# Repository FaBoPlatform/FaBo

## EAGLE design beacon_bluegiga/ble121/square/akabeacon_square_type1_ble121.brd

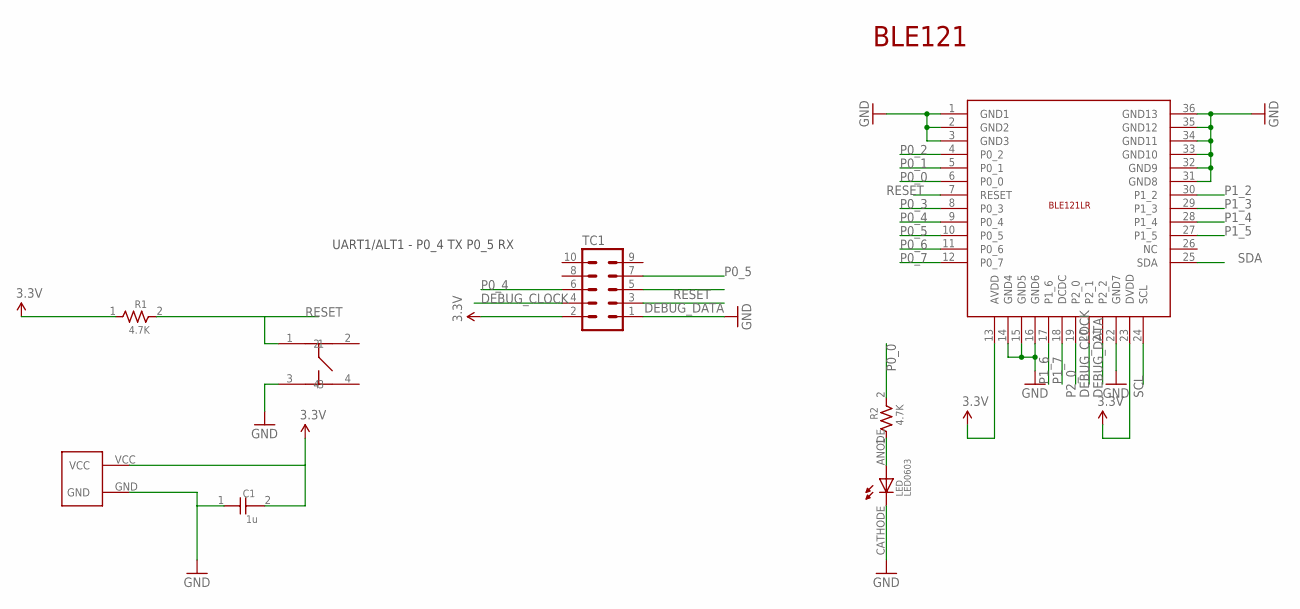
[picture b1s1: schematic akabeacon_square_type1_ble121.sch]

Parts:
BLE1: BLUEGIGA-BLE121LR
C1: 1u; 0603
LED: LED0603; 0603
R1, R2: 4.7K; 0603
TC1: TC2050-IDC-NL
U$2: SQUARE-TYPE1; SQUARE-TYPE1-TC2030
U$6: SWICTH-4P(KMR2); SWITCH-4P(KMR2)

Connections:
3.3V: BLE1.13 (AVDD), BLE1.23 (DVDD), C1.2, R1.1, TC1.2, U$2.VCC
DEBUG_CLOCK: BLE1.20 (P2_1), TC1.4
DEBUG_DATA: BLE1.21 (P2_2), TC1.3
GND: BLE1.1 (GND1), BLE1.2 (GND2), BLE1.3 (GND3), BLE1.22 (GND7), BLE1.31 (GND8), BLE1.32 (GND9), BLE1.33 (GND10), BLE1.34 (GND11), BLE1.35 (GND12), BLE1.36 (GND13), C1.1, LED.CATHODE, TC1.1, U$2.GND, U$6.3
unnamed: LED.ANODE, R2.1
unnamed: BLE1.14 (GND4), BLE1.15 (GND5), BLE1.16 (GND6)
P0_0: BLE1.6 (P0_0), R2.2
P0_1: BLE1.5 (P0_1)
P0_2: BLE1.4 (P0_2)
P0_3: BLE1.8 (P0_3)
P0_4: BLE1.9 (P0_4), TC1.6
P0_5: BLE1.10 (P0_5), TC1.7
P0_6: BLE1.11 (P0_6)
P0_7: BLE1.12 (P0_7)
P1_2: BLE1.30 (P1_2)
P1_3: BLE1.29 (P1_3)
P1_4: BLE1.28 (P1_4)
P1_5: BLE1.27 (P1_5)
P1_6: BLE1.17 (P1_6)
P1_7: BLE1.18 (DCDC)
P2_0: BLE1.19 (P2_0)
RESET: BLE1.7 (RESET), R1.2, TC1.5, U$6.1
SCL: BLE1.24 (SCL)
SDA: BLE1.25 (SDA)

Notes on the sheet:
BLE121
UART1/ALT1 - P0_4 TX P0_5 RX

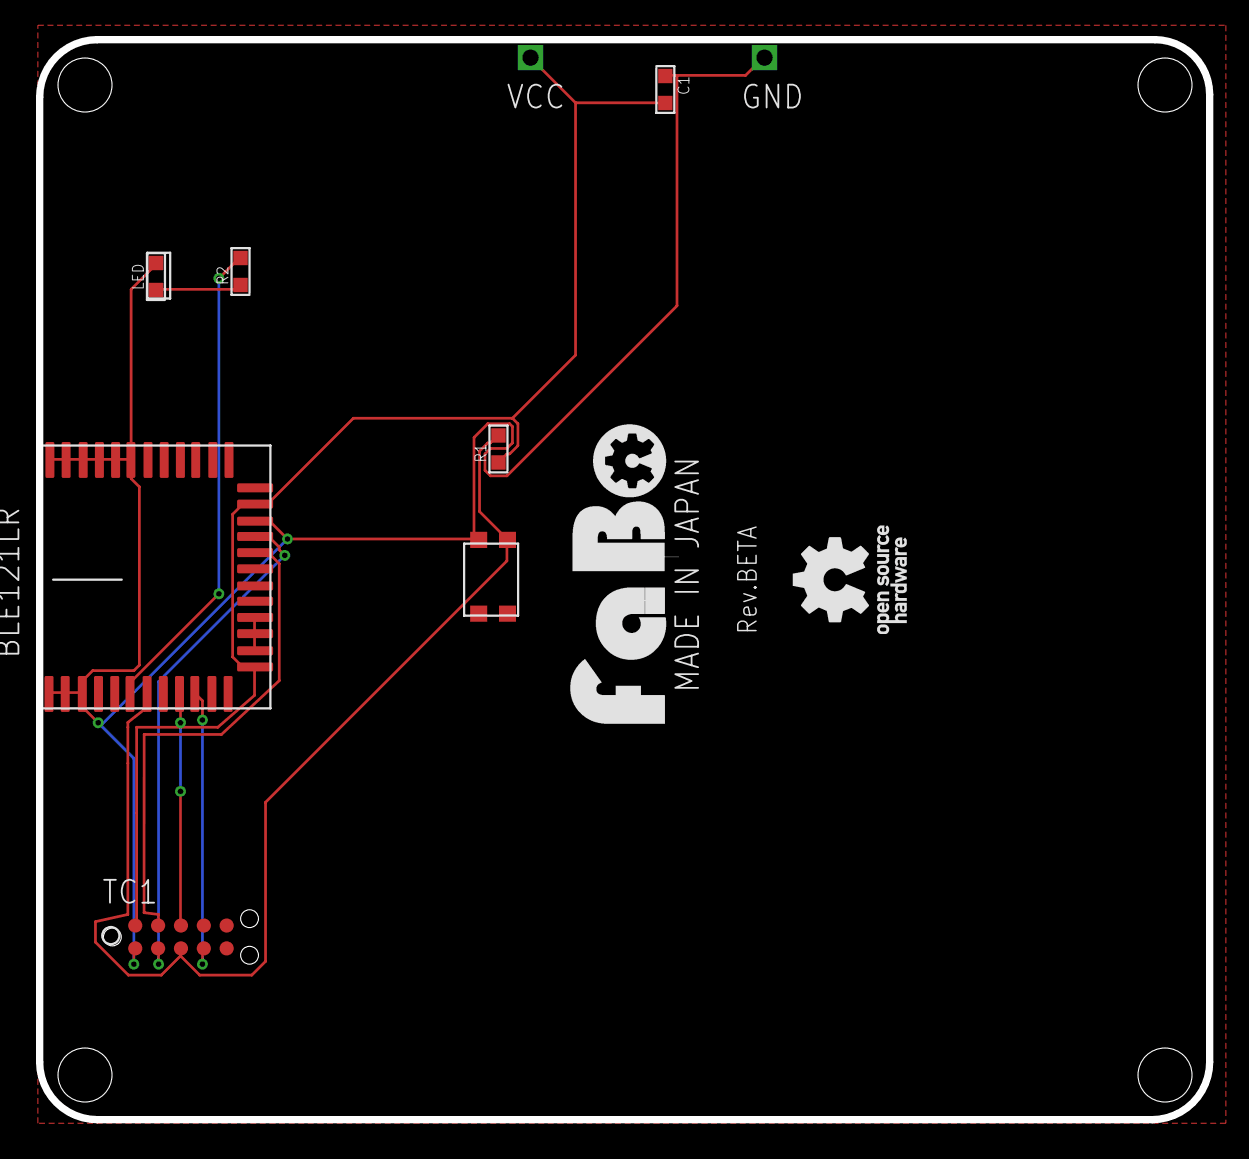
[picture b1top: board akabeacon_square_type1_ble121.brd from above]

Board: 2 copper layers, 65.0 x 60.0 mm, 8 parts (0 on the bottom side), 10 nets.

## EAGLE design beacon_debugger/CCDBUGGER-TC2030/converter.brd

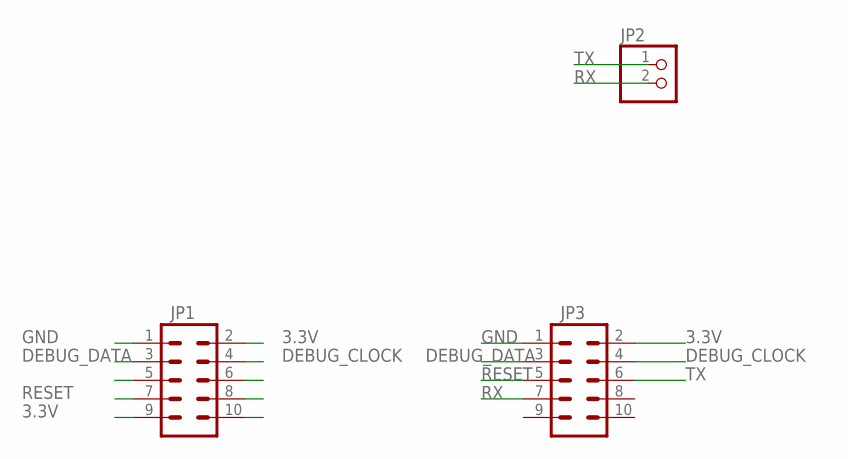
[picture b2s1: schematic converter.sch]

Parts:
JP1, JP3: M05X2SHD; 2X5-SHROUDED
JP2: PINHD-1X2; 1X02

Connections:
3.3V: JP1.2, JP1.9, JP3.2
CSN: JP1.5
DEBUG_CLOCK: JP1.4, JP3.4
DEBUG_DATA: JP1.3, JP3.3
GND: JP1.1, JP3.1
MISO: JP1.10
MOSI: JP1.8
RESET: JP1.7, JP3.5
RX: JP2.2, JP3.7
SCLK: JP1.6
TX: JP2.1, JP3.6

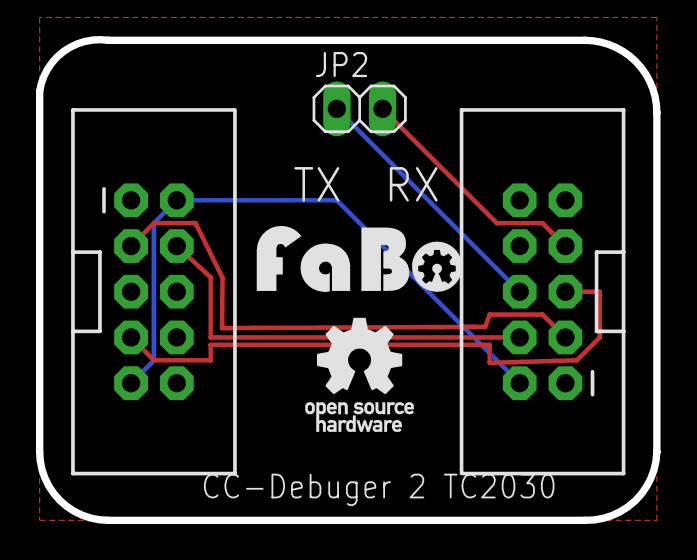
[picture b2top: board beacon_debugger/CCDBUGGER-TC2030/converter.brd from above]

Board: 2 copper layers, 34.3 x 26.7 mm, 5 parts (0 on the bottom side), 7 nets.

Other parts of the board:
U$1: LOGO_FABO_M
U$2: LOGO_OSHW_T_M

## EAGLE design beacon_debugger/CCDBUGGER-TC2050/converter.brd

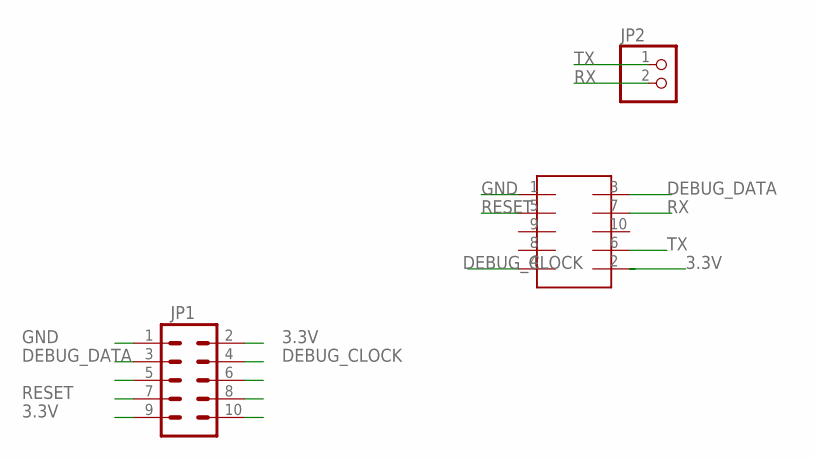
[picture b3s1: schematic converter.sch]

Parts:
JP1: M05X2SHD; 2X5-SHROUDED
JP2: PINHD-1X2; 1X02
U$4: TC-2050-SOCKET

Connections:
3.3V: JP1.2, JP1.9, U$4.2
CSN: JP1.5
DEBUG_CLOCK: JP1.4, U$4.4
DEBUG_DATA: JP1.3, U$4.3
GND: JP1.1, U$4.1
MISO: JP1.10
MOSI: JP1.8
RESET: JP1.7, U$4.5
RX: JP2.2, U$4.7
SCLK: JP1.6
TX: JP2.1, U$4.6

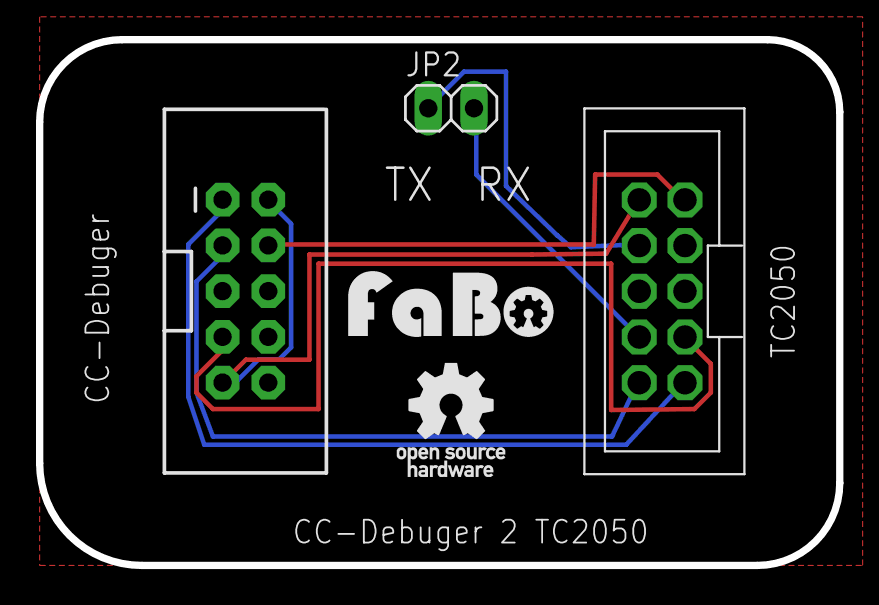
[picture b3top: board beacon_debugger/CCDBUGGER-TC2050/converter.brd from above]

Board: 2 copper layers, 44.4 x 29.2 mm, 5 parts (0 on the bottom side), 7 nets.

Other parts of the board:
U$1: LOGO_FABO_M
U$2: LOGO_OSHW_T_M

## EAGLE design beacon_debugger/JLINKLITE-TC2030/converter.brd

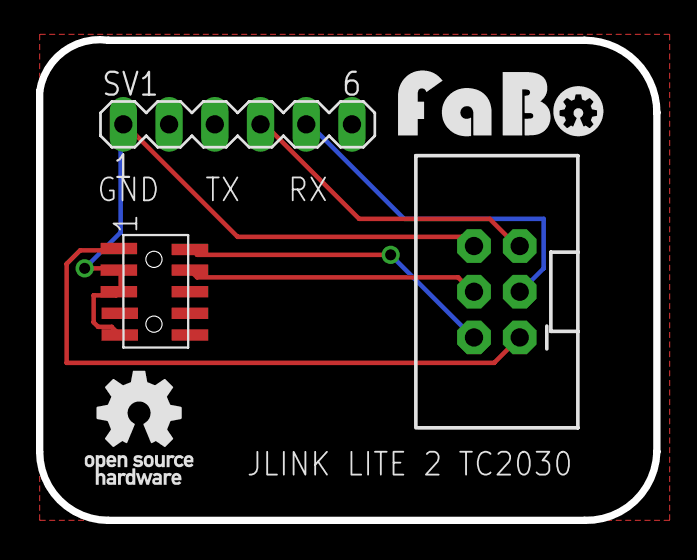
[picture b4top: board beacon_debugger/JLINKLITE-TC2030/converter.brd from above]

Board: 2 copper layers, 34.3 x 26.7 mm, 5 parts (0 on the bottom side), 6 nets.

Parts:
JP2: 2X3-SHROUDED
SV1: MA06-1
U$1: LOGO_FABO_M
U$2: LOGO_OSHW_T_M
U$5: PIN-HEADER-SMT(1.27MM)2X5

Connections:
3.3V: JP2.1, U$5.1
GND: JP2.6, SV1.1, U$5.3, U$5.5, U$5.9
P0_4: JP2.5, SV1.4
P0_5: JP2.3, SV1.5
SWCLK: JP2.4, U$5.4
SWDIO: JP2.2, U$5.2

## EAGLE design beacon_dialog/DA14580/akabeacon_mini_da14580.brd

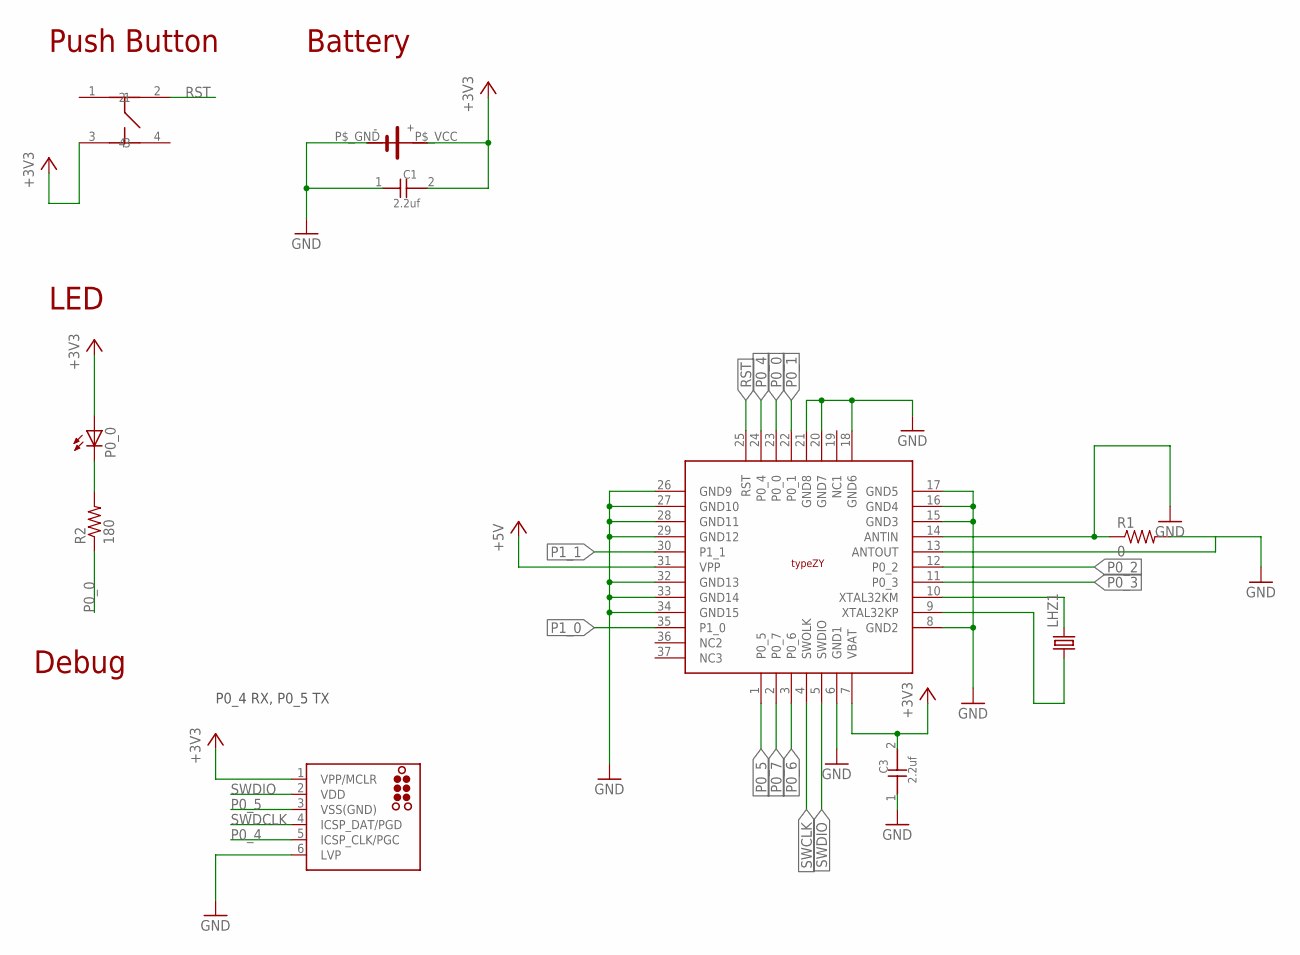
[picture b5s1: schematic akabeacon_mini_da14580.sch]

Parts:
C1, C3: 2.2uf; 0603
J2: TC2030-MCP
LHZ1: FC-12M
P0_0: LEDCHIP-LED0603; CHIP-LED0603
R1: 0; 0603-RES
R2: 180; 0603-RES
U$1: MURATA-TYPEZY; MURATA_TYPEZY
U$6: SMTU2450-BOTTOM-MINI
U$7: SWICTH-4P(KMR2); SWITCH-4P(KMR2)

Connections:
+3V3: C1.2, C3.2, J2.1 (VPP/MCLR), P0_0.A, U$1.7 (VBAT), U$6.P$_VCC, U$7.3
+5V: U$1.31 (VPP)
GND: C1.1, C3.1, J2.6 (LVP), R1.1, R1.2, U$1.6 (GND1), U$1.8 (GND2), U$1.14 (ANTIN), U$1.15 (GND3), U$1.16 (GND4), U$1.17 (GND5), U$1.18 (GND6), U$1.20 (GND7), U$1.21 (GND8), U$1.26 (GND9), U$1.27 (GND10), U$1.28 (GND11), U$1.29 (GND12), U$1.32 (GND13), U$1.33 (GND14), U$1.34 (GND15), U$6.P$_GND
LED1: P0_0.C, R2.2
P0_0: R2.1, U$1.23 (P0_0)
P0_1: U$1.22 (P0_1)
P0_2: U$1.12 (P0_2)
P0_3: U$1.11 (P0_3)
P0_4: J2.5 (ICSP_CLK/PGC), U$1.24 (P0_4)
P0_5: J2.3 (VSS(GND)), U$1.1 (P0_5)
P0_6: U$1.3 (P0_6)
P0_7: U$1.2 (P0_7)
P1_0: U$1.35 (P1_0)
P1_1: U$1.30 (P1_1)
RST: U$1.25 (RST), U$7.2
SWCLK: U$1.4 (SWOLK)
SWDCLK: J2.4 (ICSP_DAT/PGD)
SWDIO: J2.2 (VDD), U$1.5 (SWDIO)
XTAL32KM: LHZ1.2, U$1.10 (XTAL32KM)
XTAL32KP: LHZ1.1, U$1.9 (XTAL32KP)

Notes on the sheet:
Battery
Push Button
Debug
LED
P0_4 RX, P0_5 TX

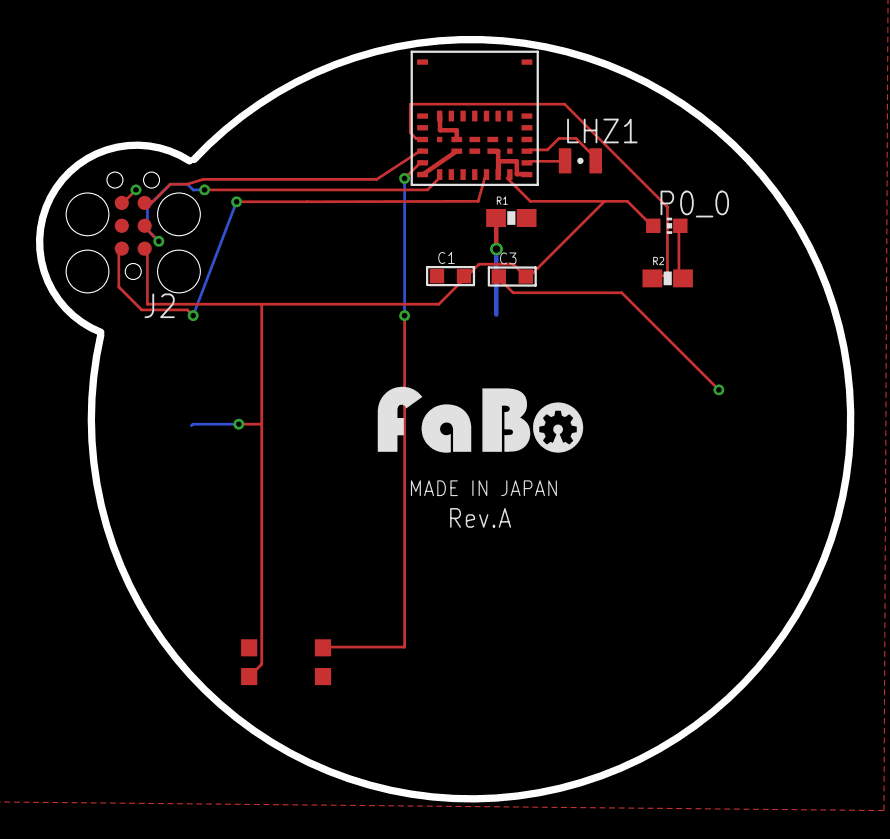
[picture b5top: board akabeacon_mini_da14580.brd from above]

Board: 2 copper layers, 45.1 x 42.2 mm, 11 parts (0 on the bottom side), 10 nets.

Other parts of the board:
U$2: LOGO_FABO_M

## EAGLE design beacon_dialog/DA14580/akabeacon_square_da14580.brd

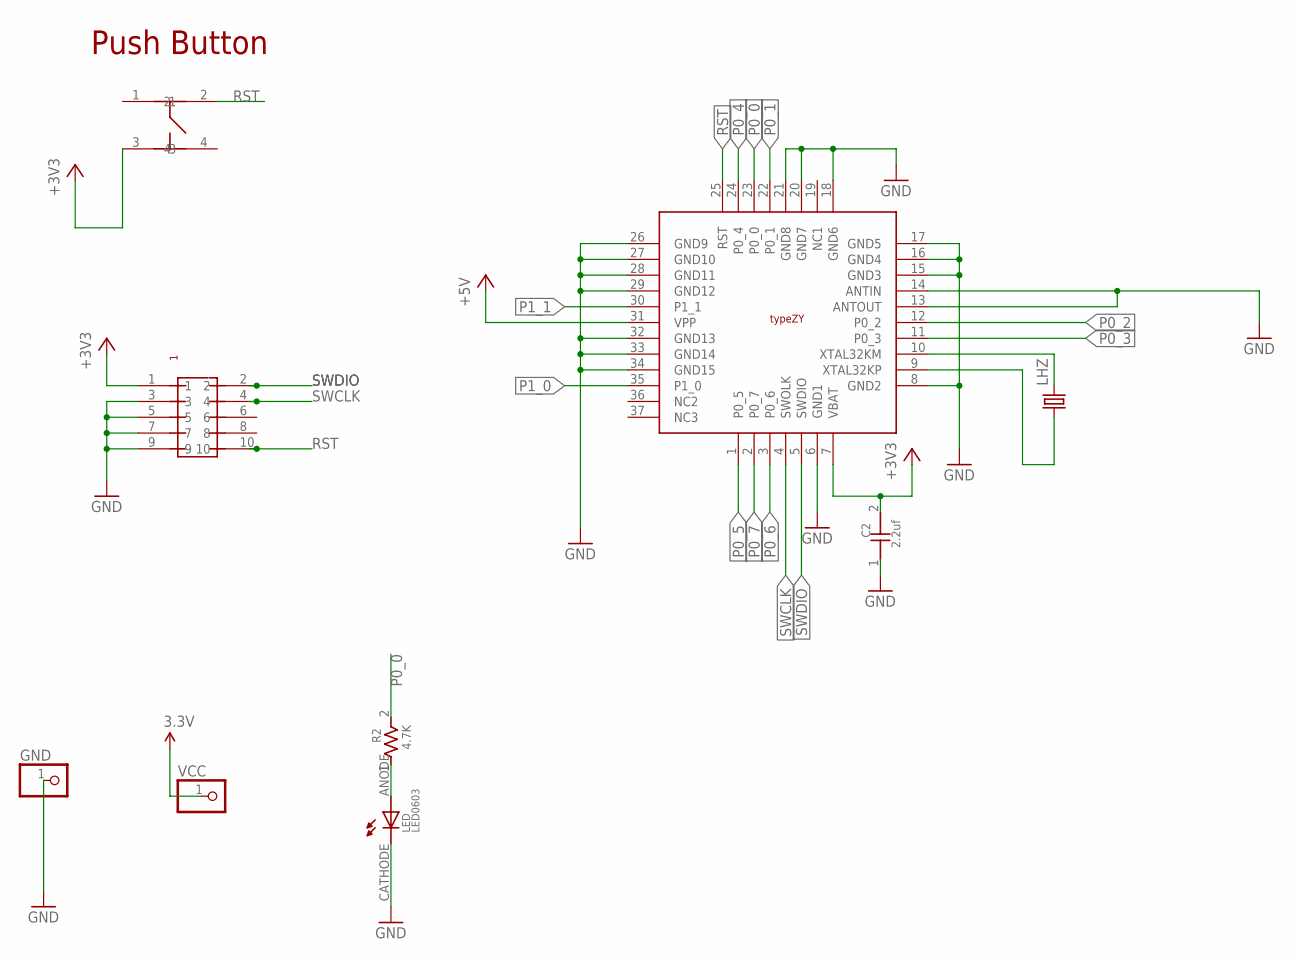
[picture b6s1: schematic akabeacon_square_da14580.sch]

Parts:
C2: 2.2uf; 0603
GND: PINHD-1X1CB; 1X01-CLEANBIG
LED: LED0603; 0603
LHZ: FC-12M
R2: 4.7K; 0603
U$6: PIN-HEADER-SMT(1.27MM)2X5
U$7: SWICTH-4P(KMR2); SWITCH-4P(KMR2)
U$9: MURATA-TYPEZY; MURATA_TYPEZY
VCC: PINHD-1X1CB; 1X01-CLEANBIG

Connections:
3.3V: VCC.1
+3V3: C2.2, U$6.1, U$7.3, U$9.7 (VBAT)
+5V: U$9.31 (VPP)
GND: C2.1, GND.1, LED.CATHODE, U$6.3, U$6.5, U$6.7, U$6.9, U$9.6 (GND1), U$9.8 (GND2), U$9.13 (ANTOUT), U$9.14 (ANTIN), U$9.15 (GND3), U$9.16 (GND4), U$9.17 (GND5), U$9.18 (GND6), U$9.20 (GND7), U$9.21 (GND8), U$9.26 (GND9), U$9.27 (GND10), U$9.28 (GND11), U$9.29 (GND12), U$9.32 (GND13), U$9.33 (GND14), U$9.34 (GND15)
unnamed: LED.ANODE, R2.1
P0_0: R2.2, U$9.23 (P0_0)
P0_1: U$9.22 (P0_1)
P0_2: U$9.12 (P0_2)
P0_3: U$9.11 (P0_3)
P0_4: U$9.24 (P0_4)
P0_5: U$9.1 (P0_5)
P0_6: U$9.3 (P0_6)
P0_7: U$9.2 (P0_7)
P1_0: U$9.35 (P1_0)
P1_1: U$9.30 (P1_1)
RST: U$6.10, U$7.2, U$9.25 (RST)
SWCLK: U$6.4, U$9.4 (SWOLK)
SWDIO: U$6.2, U$9.5 (SWDIO)
XTAL32KM: LHZ.2, U$9.10 (XTAL32KM)
XTAL32KP: LHZ.1, U$9.9 (XTAL32KP)

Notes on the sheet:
Push Button

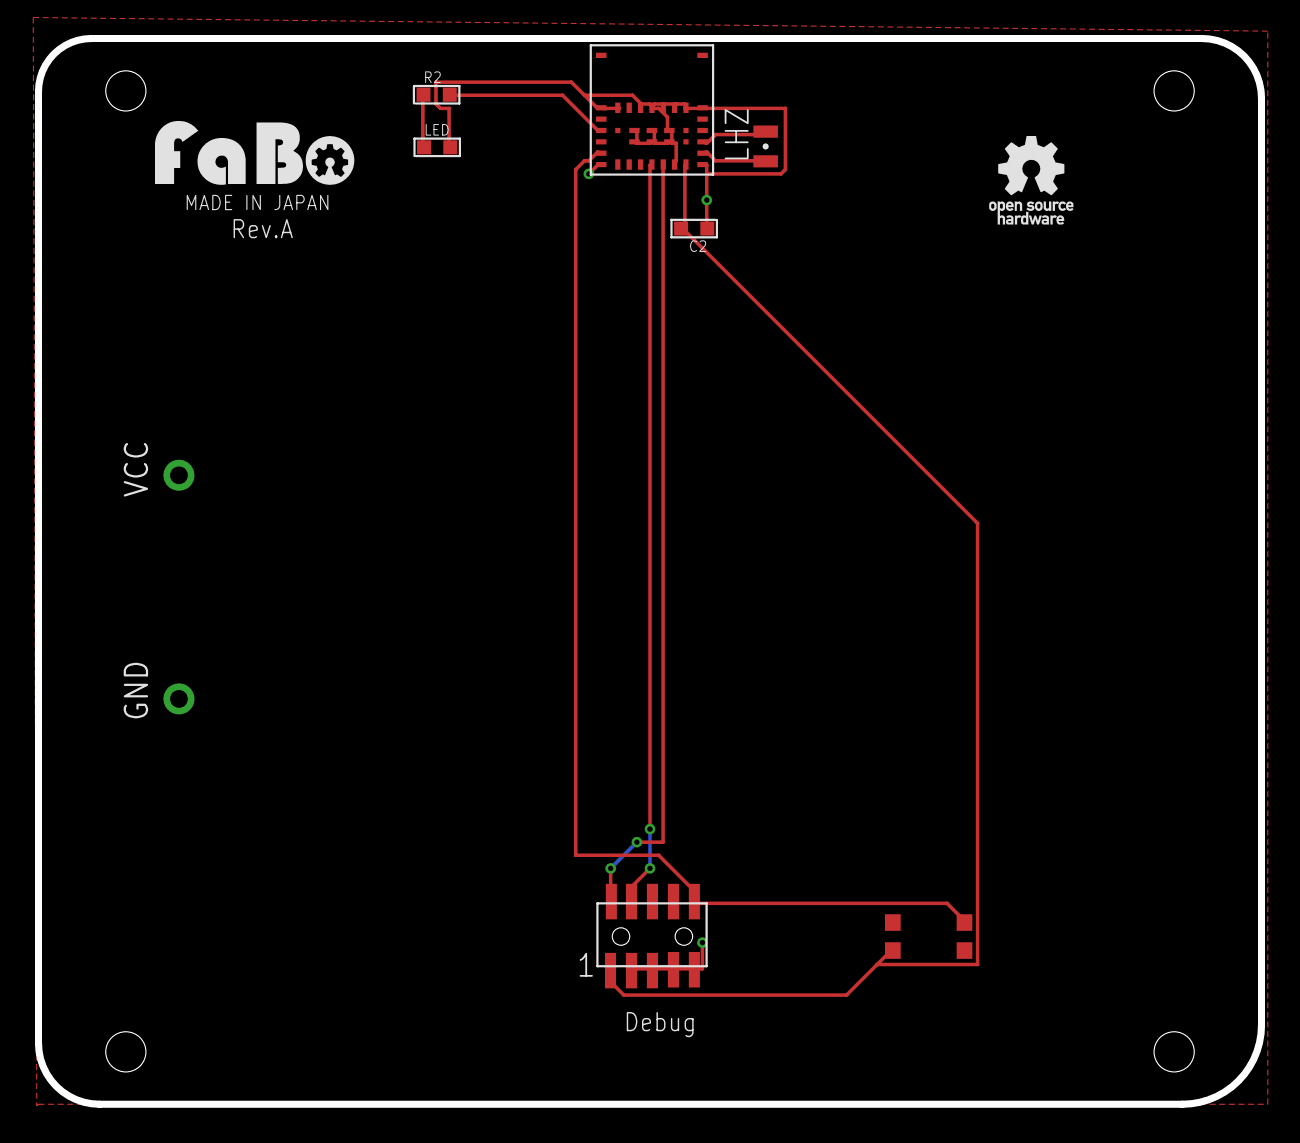
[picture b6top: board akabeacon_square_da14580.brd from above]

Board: 2 copper layers, 70.0 x 61.0 mm, 11 parts (0 on the bottom side), 9 nets.

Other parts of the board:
U$2: LOGO_FABO_M
U$4: LOGO_OSHW_T_M

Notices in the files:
parts and their libraries:
SparkFun: Licensing: CC v3.0 Share-Alike You are welcome to use this library for commercial purposes.
tag-connect: ©2009 ROFA.cz - modified and updated by Robert Darlington ‹rdarlington@gmail.com›
